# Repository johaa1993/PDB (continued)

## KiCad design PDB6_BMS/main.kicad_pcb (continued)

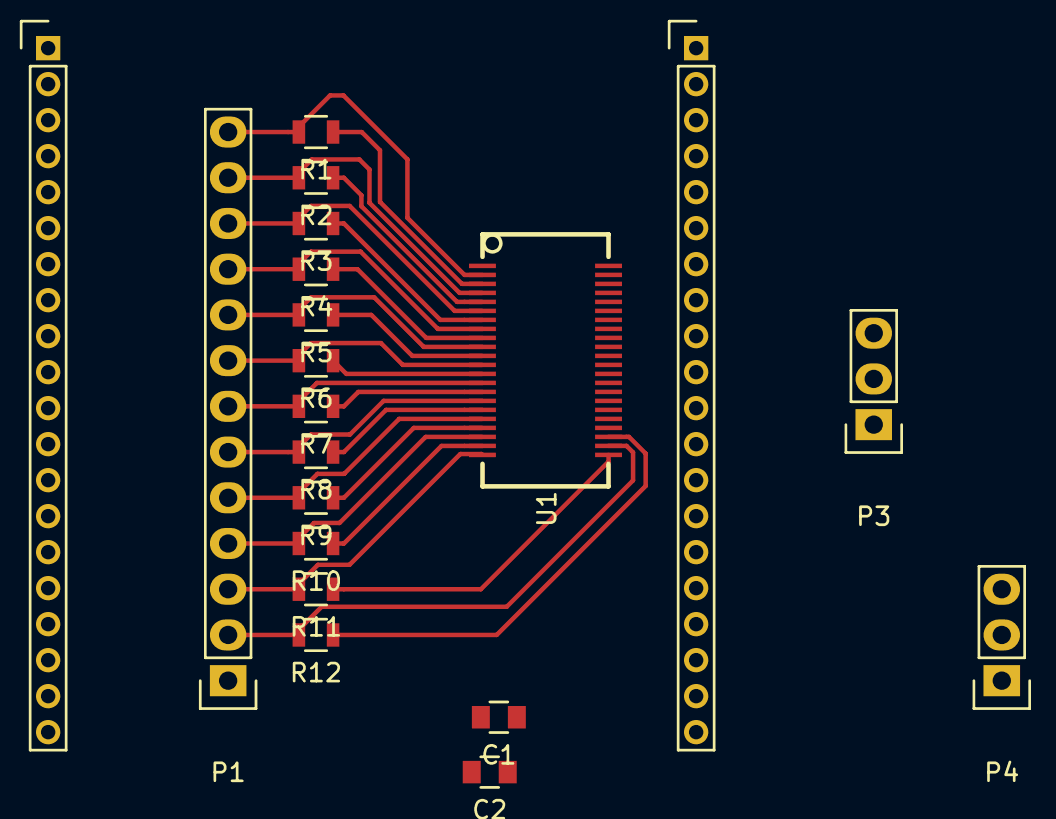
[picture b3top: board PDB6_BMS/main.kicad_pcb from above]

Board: 2 copper layers, 20 parts (0 on the bottom side), 33 nets.

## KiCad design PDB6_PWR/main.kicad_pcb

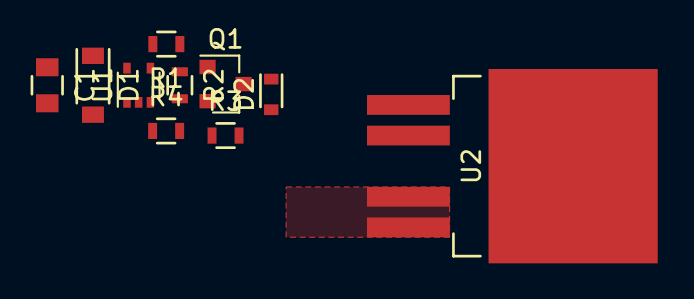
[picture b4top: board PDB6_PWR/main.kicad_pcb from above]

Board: 2 copper layers, 10 parts (0 on the bottom side), 7 nets, no tracks yet.

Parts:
C1: C; C_0805
D1: 5V; SOD-123
D2: D; D_0603
Q1: BC847CE6327HTSA1; SOT-23
R1, R2, R3, R4: R; R_0603
U1: 74LVC1G08; SOT-353
U2: AUIPS7111S; TO-263-5Lead

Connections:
+3V3: C1.1, D1.1, U1.5
/Power_Out: U2.4, U2.5
GND: C1.2, D1.2, D2.2, Q1.2, R2.2, R4.1, U1.3
unnamed: D2.1, Q1.3, U2.1
unnamed: Q1.1, R1.1, R2.1
unnamed: R1.2, U1.4
unnamed: R3.1, R4.2, U2.2

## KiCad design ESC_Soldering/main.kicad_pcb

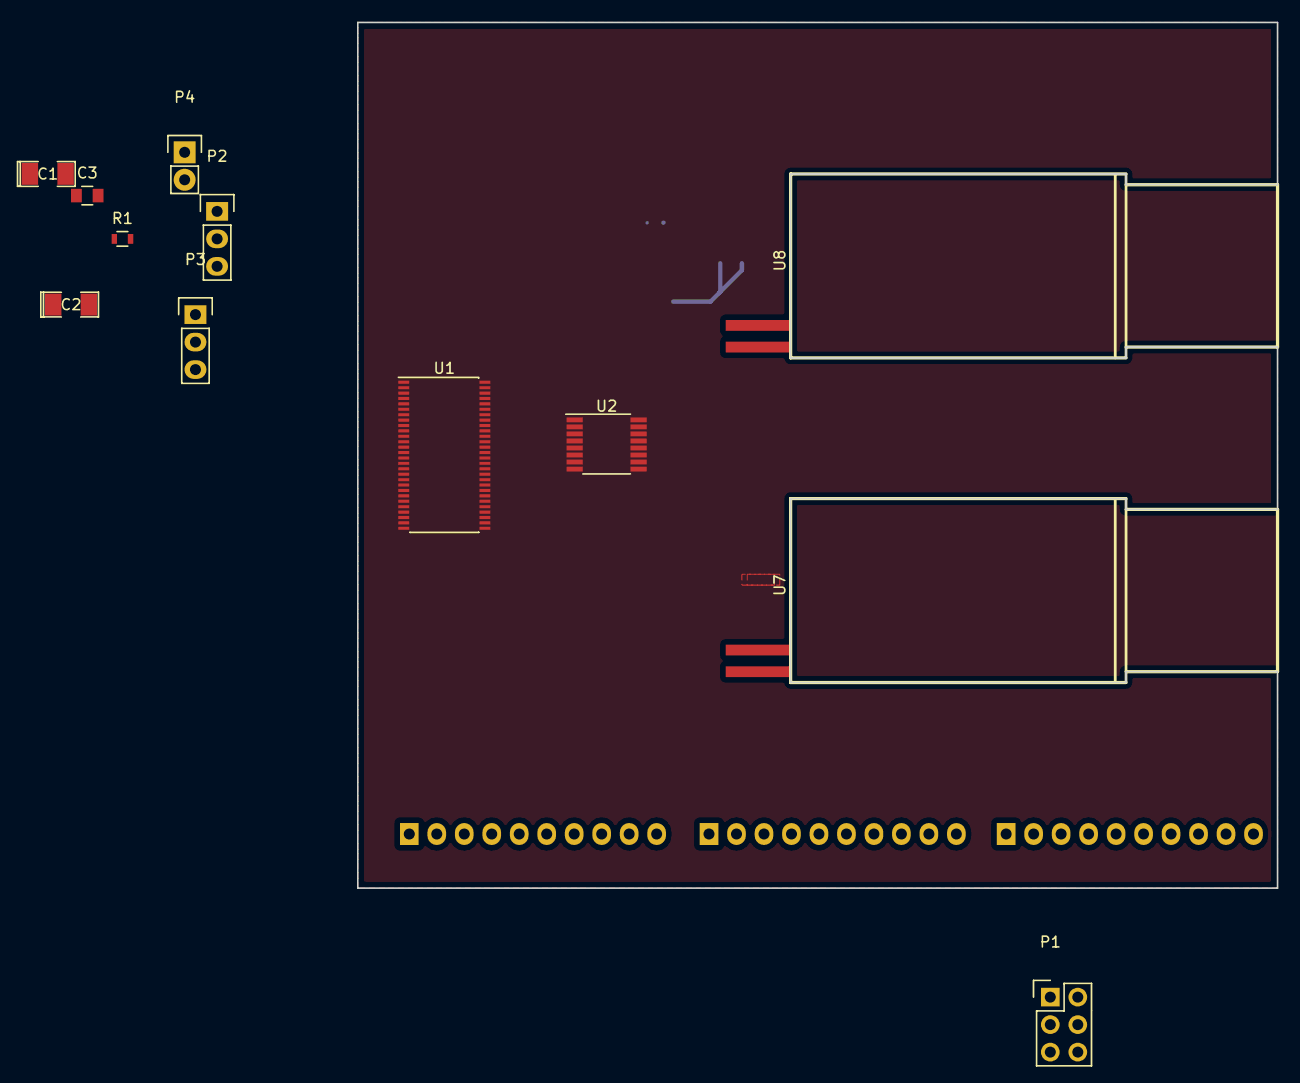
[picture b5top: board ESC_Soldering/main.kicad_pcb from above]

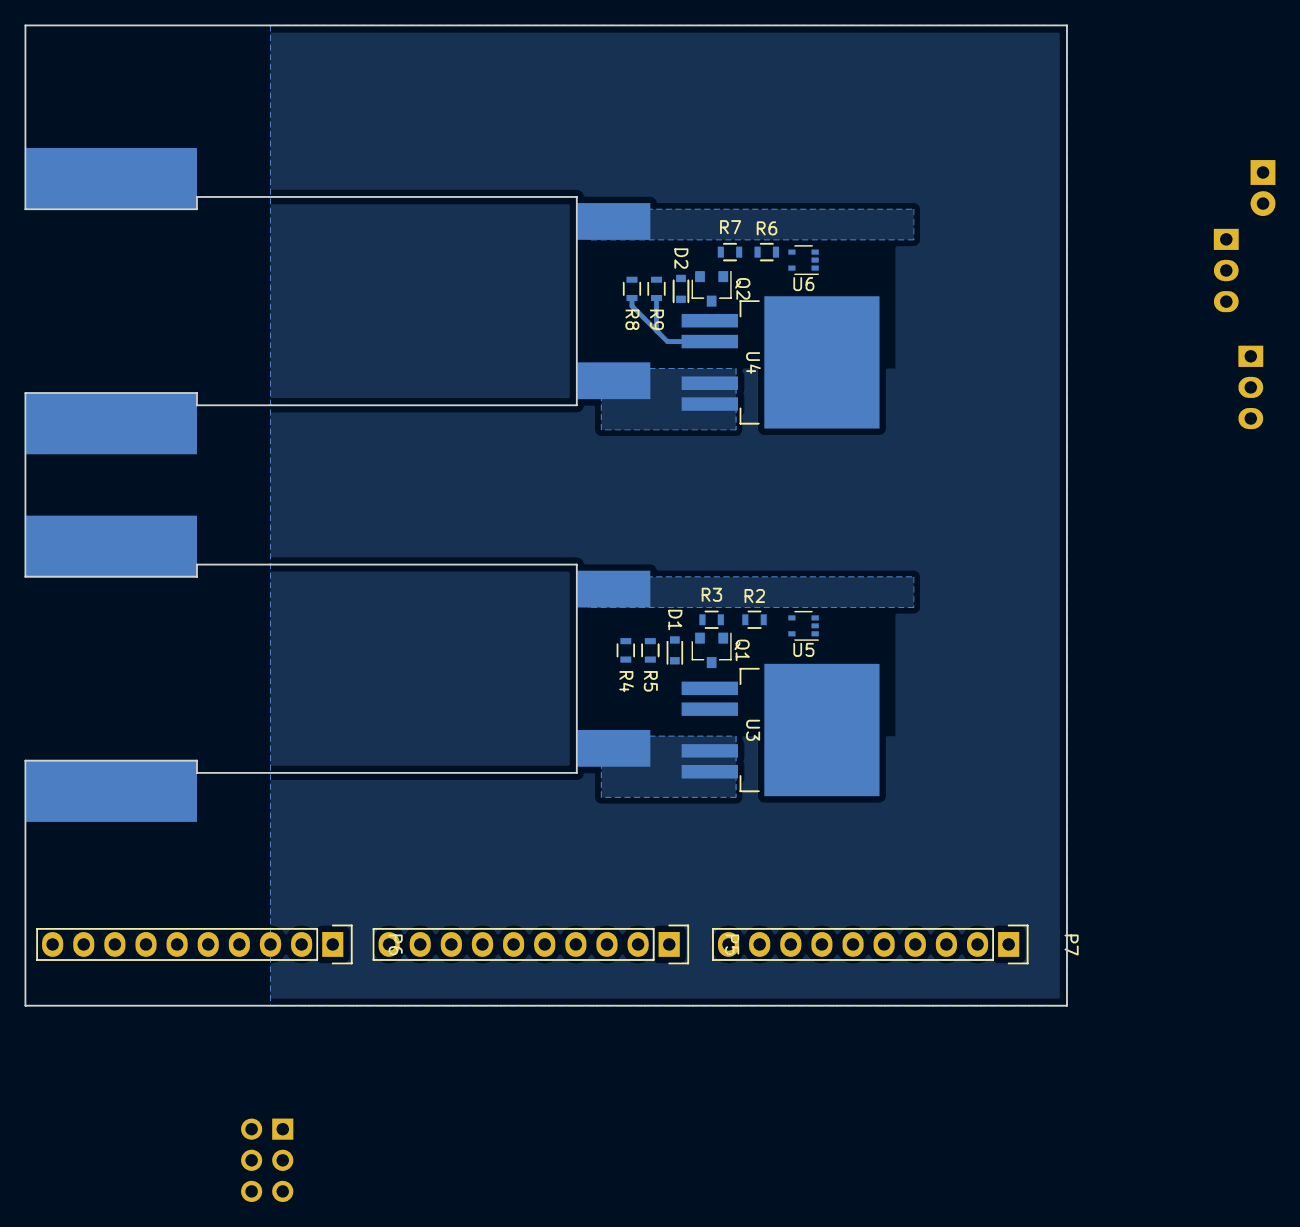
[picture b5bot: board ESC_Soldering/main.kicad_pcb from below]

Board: 2 copper layers, 85.0 x 80.0 mm, 31 parts (19 on the bottom side), 32 nets.

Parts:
C1, C2: CP; SMD-1206_Pol
C3: C; C_0805
D1, D2: D; D_0603
P1: CONN_02X03; Pin_Header_Straight_2x03
P2, P3: CONN_01X03; Pin_Header_Straight_1x03
P4: CONN_01X02; Pin_Header_Straight_1x02
P5, P6, P7: CONN_01X10; Pin_Header_Straight_1x10
Q1, Q2: BC847CE6327HTSA1; SOT-23
R1, R2, R3, R4, R5, R6, R7, R8, R9: R; R_0603
U1: PCA9698; TSSOP-56_6.1x14mm_Pitch0.5mm
U2: ADS7828; TSSOP-16_4.4x5mm_Pitch0.65mm
U3, U4: AUIPS7111S; TO-263-5Lead
U5, U6: 74LVC1G08; SOT-353
U7, U8: Littlebee

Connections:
+3V3: C1.1, P1.2, P2.3, P3.3, P4.1, R1.2, U1.18, U1.46, U5.5, U6.5
+BATT: U3.3, U4.3
/CH1: P7.1, R4.2, U2.1
/CH2: P7.2, R8.2, U2.2
/CH3: P7.3, U2.3
/CH4: P7.4, U2.4
/CH5: P7.5, U2.5
/CH6: P7.6, U2.6
/CH7: P7.7, U2.7
/CH8: P7.8, U2.8
/Enable_1: P5.1, U1.3, U5.1
/Enable_2: P5.2, U1.4, U6.1
/PWM1: P6.1, U7.4
/PWM2: P6.2, U8.4
/SCL: P1.5, U1.2, U2.14
/SDA: P1.3, U1.1, U2.15
/pwr_mod_1/Power_Enanle_B: P4.2, U5.2, U6.2
/pwr_mod_1/Power_Out: U3.4, U3.5, U7.1
/pwr_mod_2/Power_Out: U4.4, U4.5, U8.1
GND: C1.2, C2.2, C3.2, D1.2, D2.2, P1.1, P2.1, P3.1, Q1.2, Q2.2, R3.2, R5.1, R7.2, R9.1, U1.6, U1.11, U1.23, U1.34, U1.39, U1.51, U2.9, U2.11, U5.3, U6.3, U7.2, U7.3, U8.2, U8.3
unnamed: C2.1, R1.1, U2.16
unnamed: C3.1, U2.10
unnamed: D1.1, Q1.3, U3.1
unnamed: D2.1, Q2.3, U4.1
unnamed: P2.2, U2.13
unnamed: P3.2, U2.12
unnamed: Q1.1, R2.1, R3.1
unnamed: Q2.1, R6.1, R7.1
unnamed: R2.2, U5.4
unnamed: R4.1, R5.2, U3.2
unnamed: R6.2, U6.4
unnamed: R8.1, R9.2, U4.2

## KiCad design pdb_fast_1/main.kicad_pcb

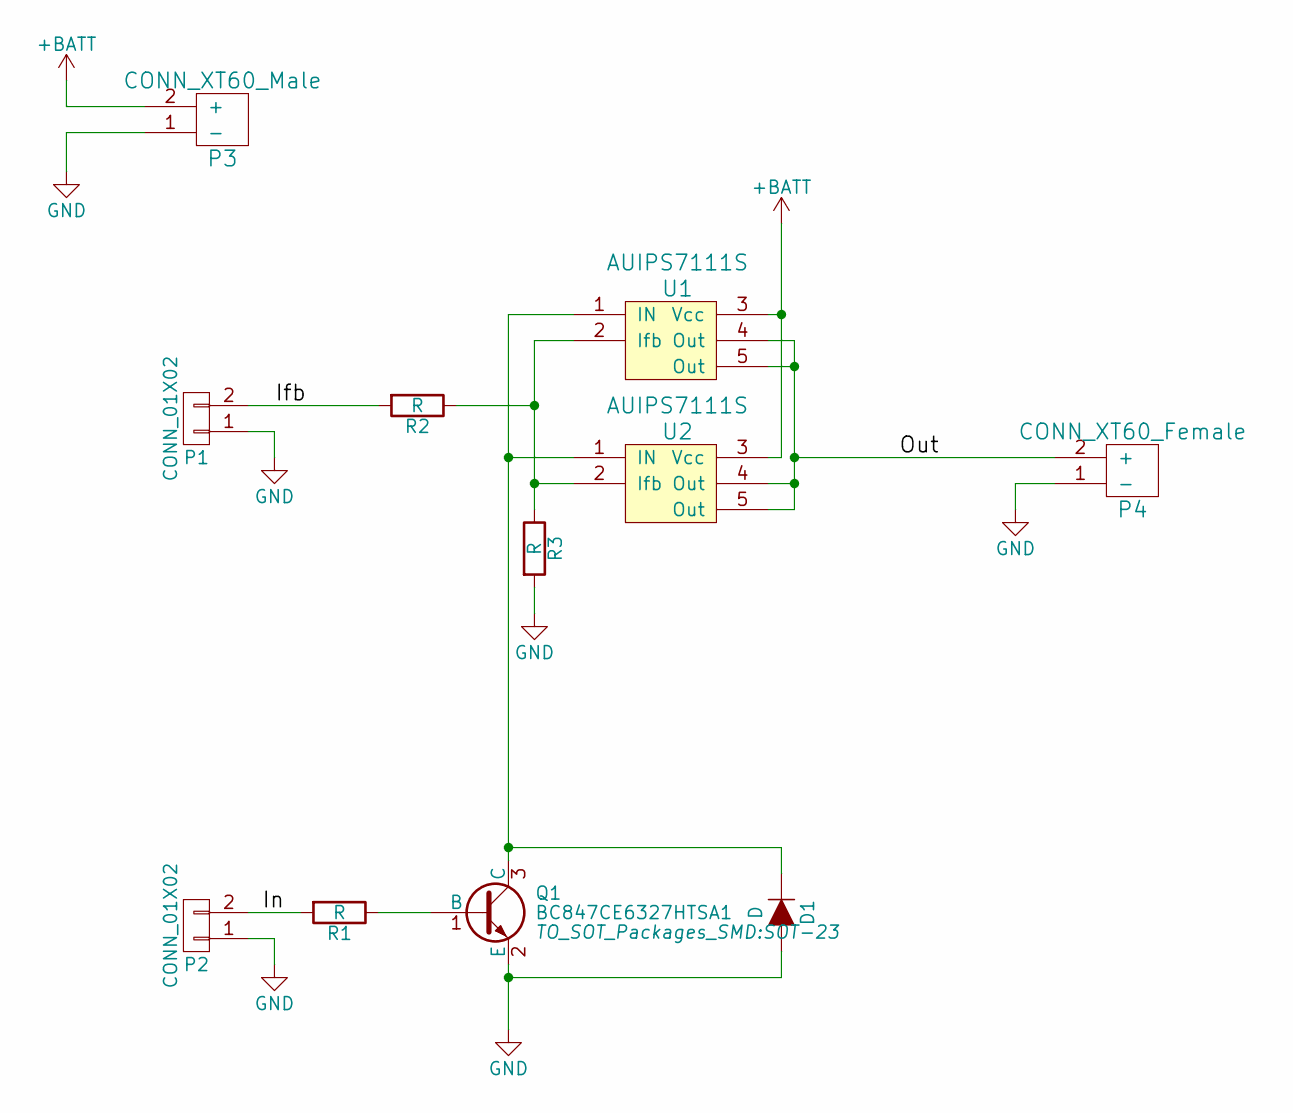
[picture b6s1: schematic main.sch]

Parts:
D1: D; SOD-123
P1, P2: CONN_01X02; Pin_Header_Straight_1x02
P3: CONN_XT60_Male; CONN_XT60_Male1_Horizontal
P4: CONN_XT60_Female; CONN_XT60_Male2_Horizontal
Q1: BC847CE6327HTSA1; SOT-23
R1, R2, R3: R; R_0603
U1, U2: AUIPS7111S; TO-263-!3

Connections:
+BATT: P3.2 (+), U1.3 (Vcc), U2.3 (Vcc)
/Ifb: P1.2, R2.2
/In: P2.2, R1.2
/Out: P4.2 (+), U1.4 (Out), U1.5 (Out), U2.4 (Out), U2.5 (Out)
GND: D1.2 (A), P1.1, P2.1, P3.1 (-), P4.1 (-), Q1.2 (E), R3.2
unnamed: D1.1 (K), Q1.3 (C), U1.1 (IN), U2.1 (IN)
unnamed: Q1.1 (B), R1.1
unnamed: R2.1, R3.1, U1.2 (Ifb), U2.2 (Ifb)

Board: 2 copper layers, 11 parts (0 on the bottom side), 8 nets, no tracks yet.

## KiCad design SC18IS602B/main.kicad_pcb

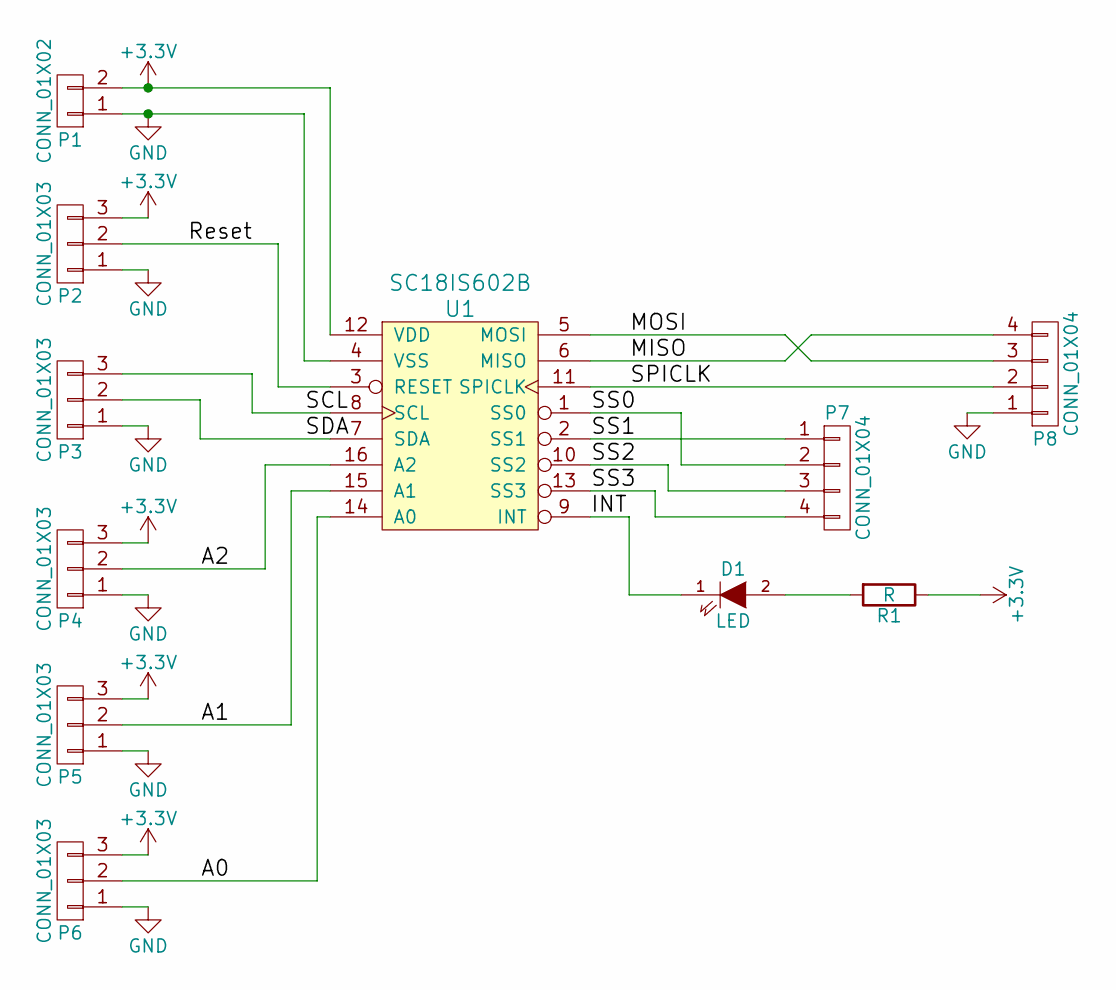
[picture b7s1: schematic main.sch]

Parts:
D1: LED; LED_0805
P1: CONN_01X02; Pin_Header_Straight_1x02
P2, P3, P4, P5, P6: CONN_01X03; Pin_Header_Straight_1x03
P7, P8: CONN_01X04; Pin_Header_Straight_1x04
R1: R; Resistor_Horizontal_RM7mm
U1: SC18IS602B; TSSOP-16_4.4x5mm_Pitch0.65mm

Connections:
+3V3: P1.2, P2.3, P4.3, P5.3, P6.3, R1.1, U1.12 (VDD)
/A0: P6.2, U1.14 (A0)
/A1: P5.2, U1.15 (A1)
/A2: P4.2, U1.16 (A2)
/INT: D1.1 (K), U1.9 (INT)
/MISO: P8.4, U1.6 (MISO)
/MOSI: P8.3, U1.5 (MOSI)
/Reset: P2.2, U1.3 (RESET)
/SCL: P3.3, U1.8 (SCL)
/SDA: P3.2, U1.7 (SDA)
/SPICLK: P8.2, U1.11 (SPICLK)
/SS0: P7.2, U1.1 (SS0)
/SS1: P7.1, U1.2 (SS1)
/SS2: P7.3, U1.10 (SS2)
/SS3: P7.4, U1.13 (SS3)
GND: P1.1, P2.1, P3.1, P4.1, P5.1, P6.1, P8.1, U1.4 (VSS)
unnamed: D1.2 (A), R1.2

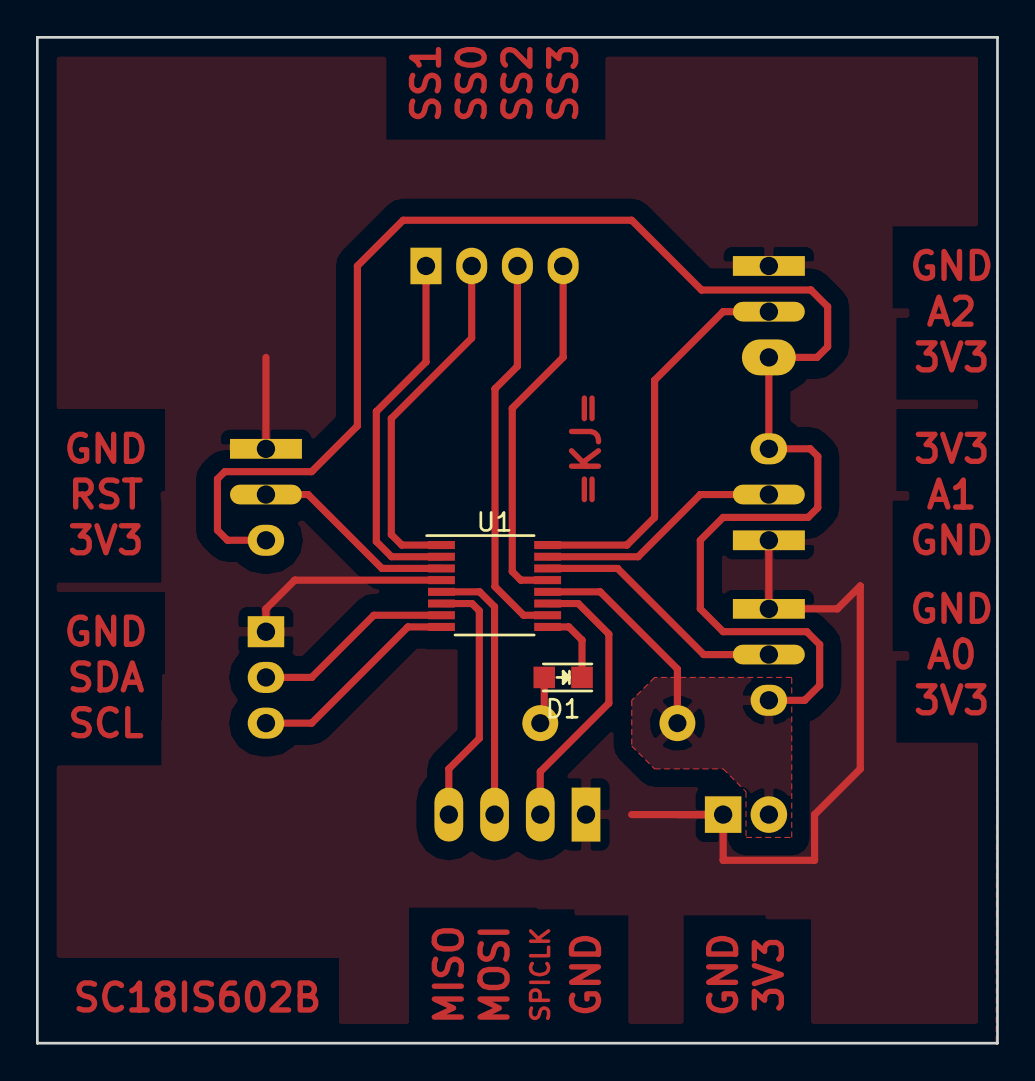
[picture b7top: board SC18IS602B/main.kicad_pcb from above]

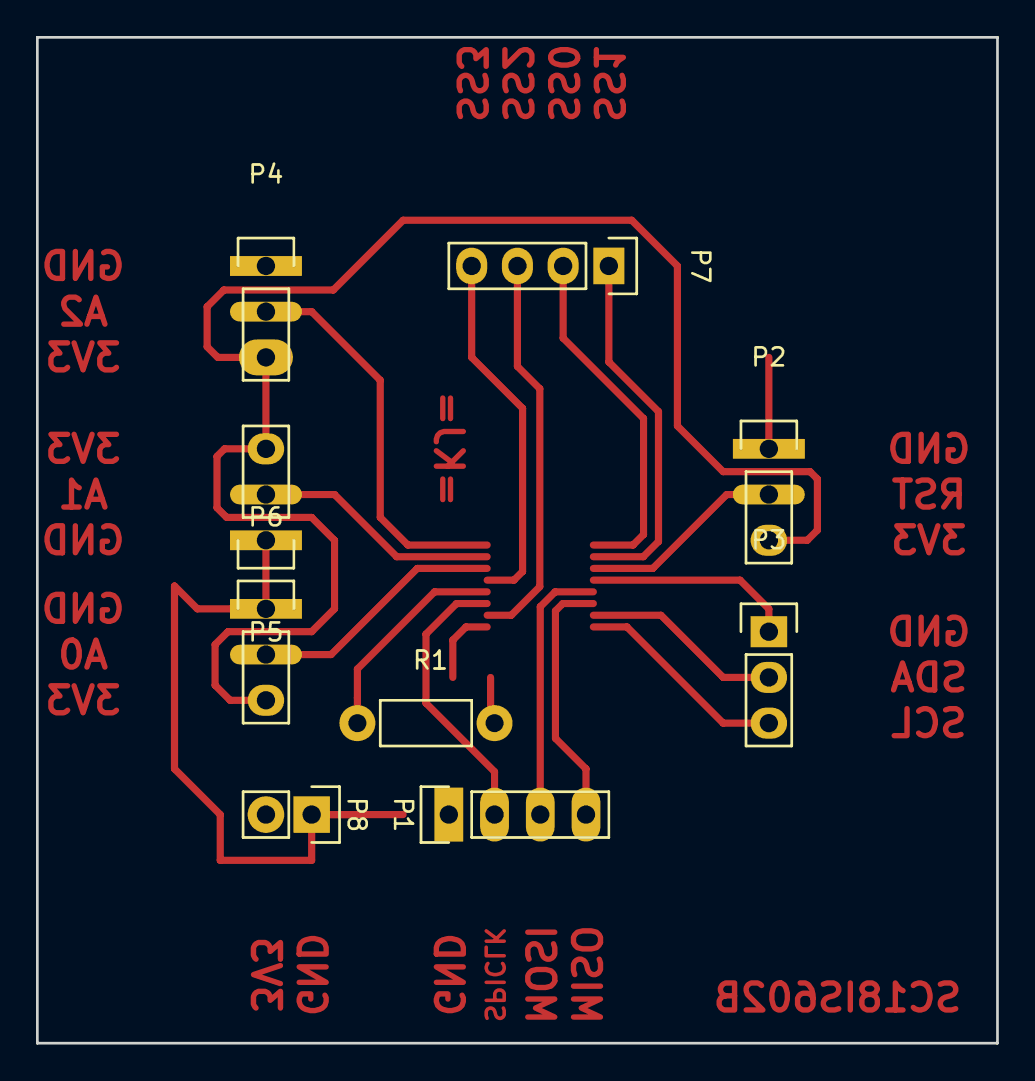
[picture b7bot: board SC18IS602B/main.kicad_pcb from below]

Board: 2 copper layers, 53.3 x 55.9 mm, 11 parts (9 on the bottom side), 17 nets.

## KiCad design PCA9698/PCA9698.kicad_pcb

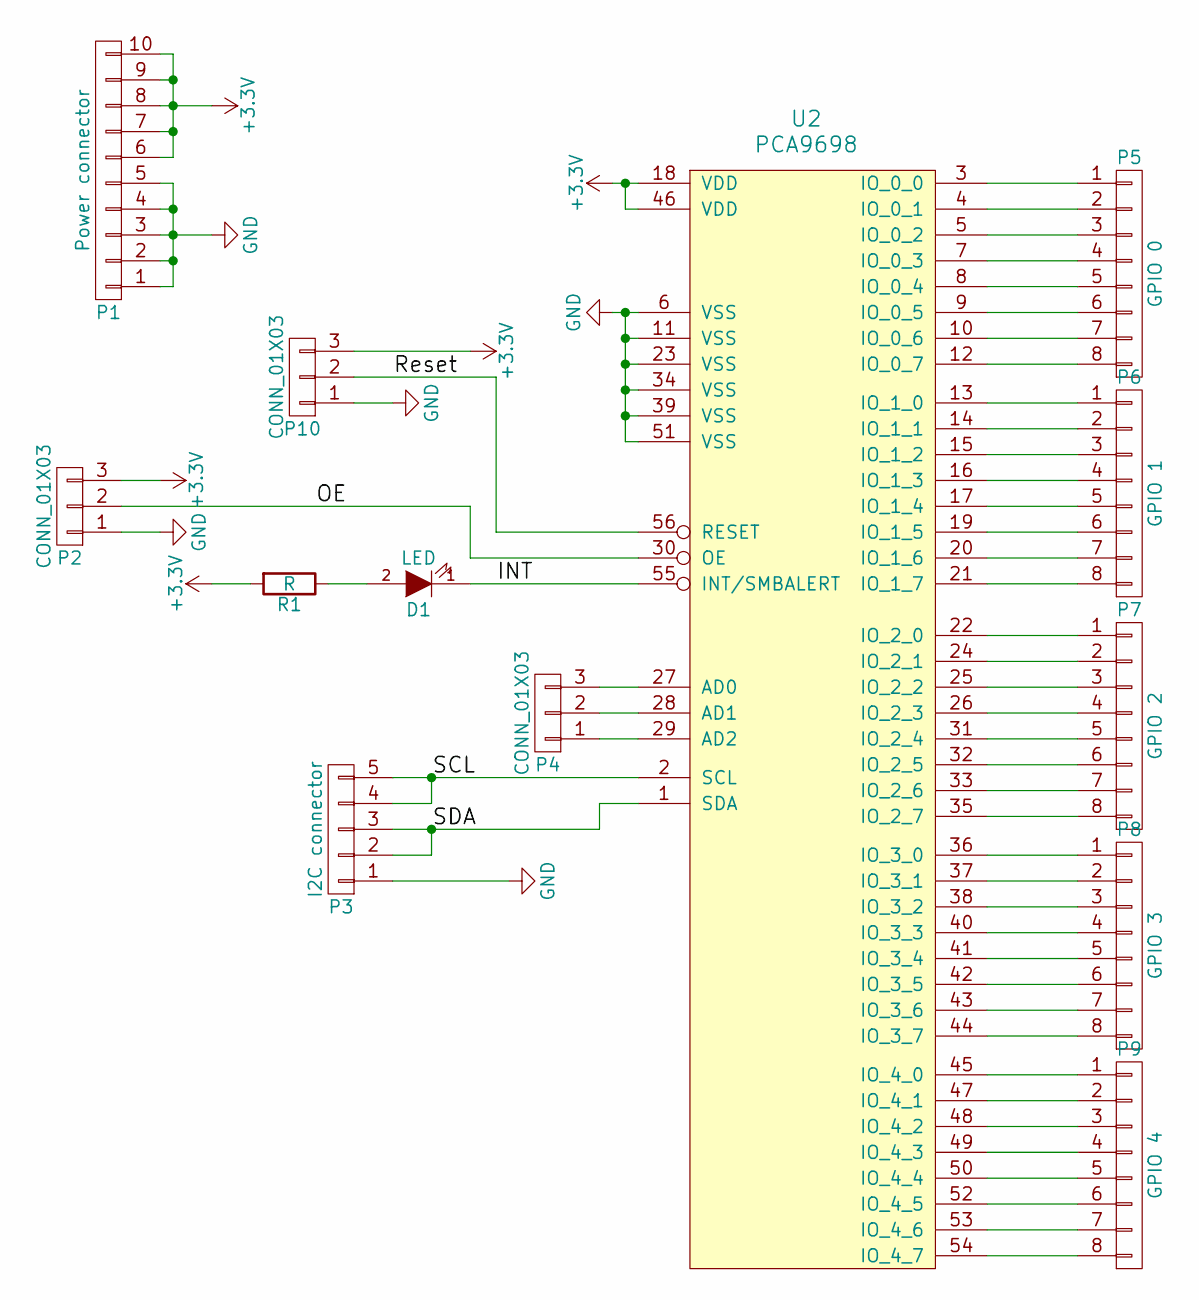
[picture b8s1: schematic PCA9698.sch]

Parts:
D1: LED; LED_0805
P1: Power connector; Pin_Header_Straight_1x10
P2, P4, P10: CONN_01X03; Pin_Header_Straight_1x03
P3: I2C connector; Pin_Header_Straight_1x05
P5: GPIO 0; Pin_Header_Straight_1x08
P6: GPIO 1; Pin_Header_Straight_1x08
P7: GPIO 2; Pin_Header_Straight_1x08
P8: GPIO 3; Pin_Header_Straight_1x08
P9: GPIO 4; Pin_Header_Straight_1x08
R1: R; R_0805
U2: PCA9698; TSSOP-56_6.1x14mm_Pitch0.5mm

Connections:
+3V3: P1.6, P1.7, P1.8, P1.9, P1.10, P2.3, P10.3, R1.2, U2.18 (VDD), U2.46 (VDD)
/INT: D1.1 (K), U2.55 (INT/SMBALERT)
/OE: P2.2, U2.30 (OE)
/Reset: P10.2, U2.56 (RESET)
/SCL: P3.4, P3.5, U2.2 (SCL)
/SDA: P3.2, P3.3, U2.1 (SDA)
GND: P1.1, P1.2, P1.3, P1.4, P1.5, P2.1, P3.1, P10.1, U2.6 (VSS), U2.11 (VSS), U2.23 (VSS), U2.34 (VSS), U2.39 (VSS), U2.51 (VSS)
unnamed: D1.2 (A), R1.1
unnamed: P4.1, U2.29 (AD2)
unnamed: P4.2, U2.28 (AD1)
unnamed: P4.3, U2.27 (AD0)
unnamed: P5.1, U2.3 (IO_0_0)
unnamed: P5.2, U2.4 (IO_0_1)
unnamed: P5.3, U2.5 (IO_0_2)
unnamed: P5.4, U2.7 (IO_0_3)
unnamed: P5.5, U2.8 (IO_0_4)
unnamed: P5.6, U2.9 (IO_0_5)
unnamed: P5.7, U2.10 (IO_0_6)
unnamed: P5.8, U2.12 (IO_0_7)
unnamed: P6.1, U2.13 (IO_1_0)
unnamed: P6.2, U2.14 (IO_1_1)
unnamed: P6.3, U2.15 (IO_1_2)
unnamed: P6.4, U2.16 (IO_1_3)
unnamed: P6.5, U2.17 (IO_1_4)
unnamed: P6.6, U2.19 (IO_1_5)
unnamed: P6.7, U2.20 (IO_1_6)
unnamed: P6.8, U2.21 (IO_1_7)
unnamed: P7.1, U2.22 (IO_2_0)
unnamed: P7.2, U2.24 (IO_2_1)
unnamed: P7.3, U2.25 (IO_2_2)
unnamed: P7.4, U2.26 (IO_2_3)
unnamed: P7.5, U2.31 (IO_2_4)
unnamed: P7.6, U2.32 (IO_2_5)
unnamed: P7.7, U2.33 (IO_2_6)
unnamed: P7.8, U2.35 (IO_2_7)
unnamed: P8.1, U2.36 (IO_3_0)
unnamed: P8.2, U2.37 (IO_3_1)
unnamed: P8.3, U2.38 (IO_3_2)
unnamed: P8.4, U2.40 (IO_3_3)
unnamed: P8.5, U2.41 (IO_3_4)
unnamed: P8.6, U2.42 (IO_3_5)
unnamed: P8.7, U2.43 (IO_3_6)
unnamed: P8.8, U2.44 (IO_3_7)
unnamed: P9.1, U2.45 (IO_4_0)
unnamed: P9.2, U2.47 (IO_4_1)
unnamed: P9.3, U2.48 (IO_4_2)
unnamed: P9.4, U2.49 (IO_4_3)
unnamed: P9.5, U2.50 (IO_4_4)
unnamed: P9.6, U2.52 (IO_4_5)
unnamed: P9.7, U2.53 (IO_4_6)
unnamed: P9.8, U2.54 (IO_4_7)

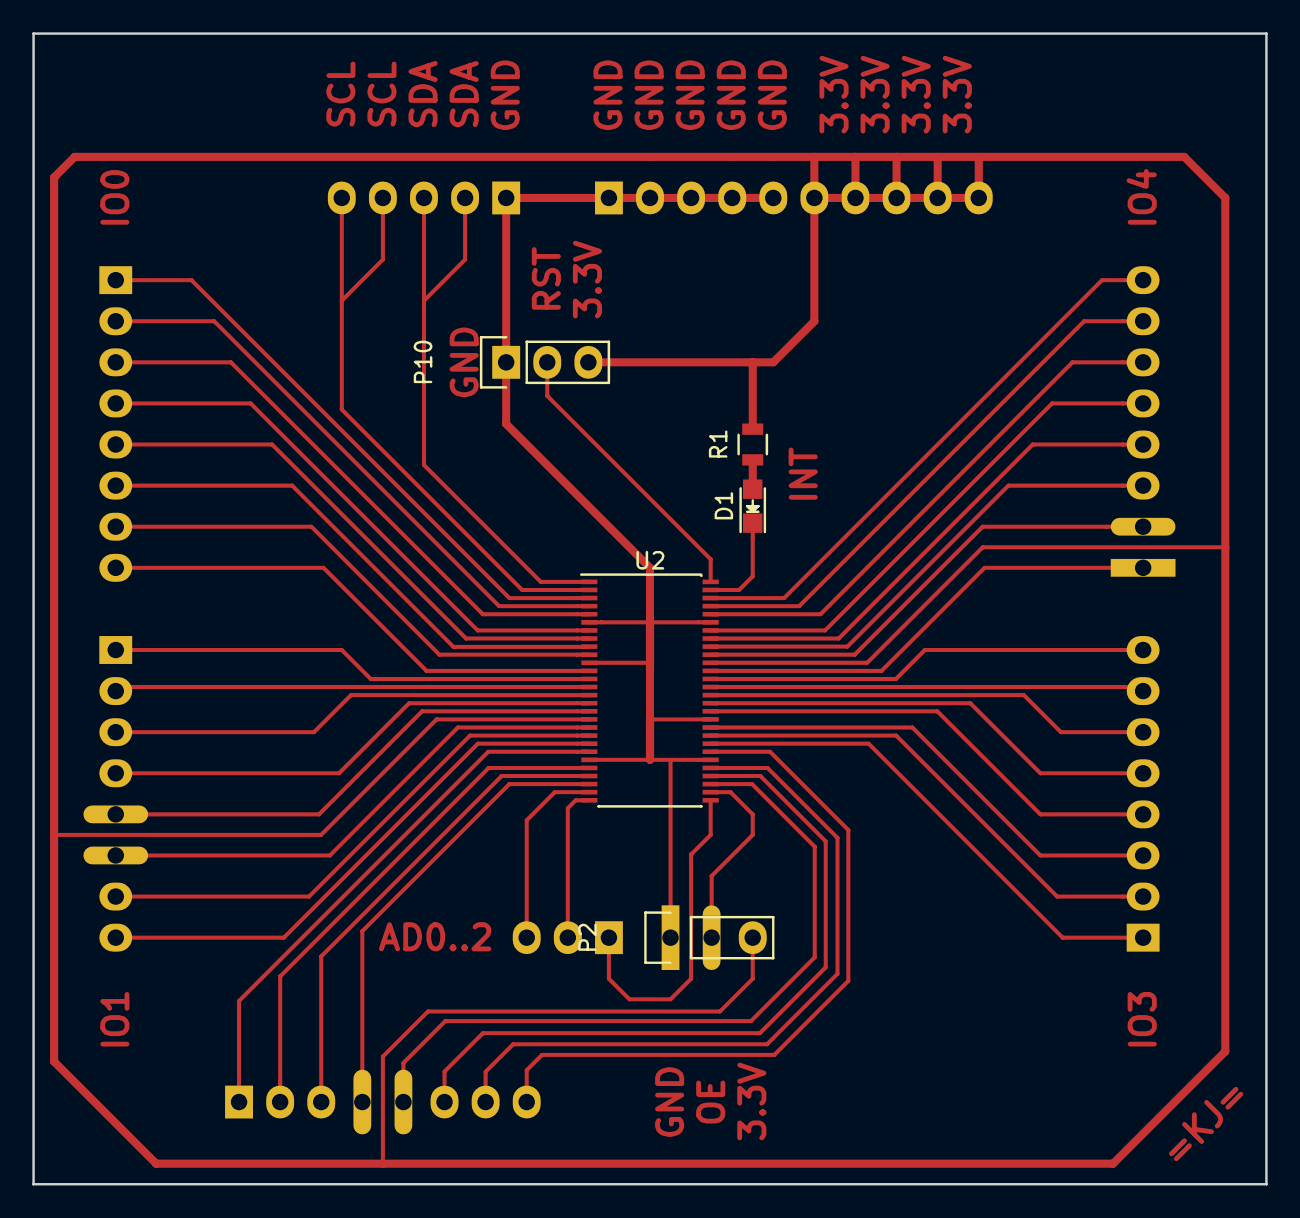
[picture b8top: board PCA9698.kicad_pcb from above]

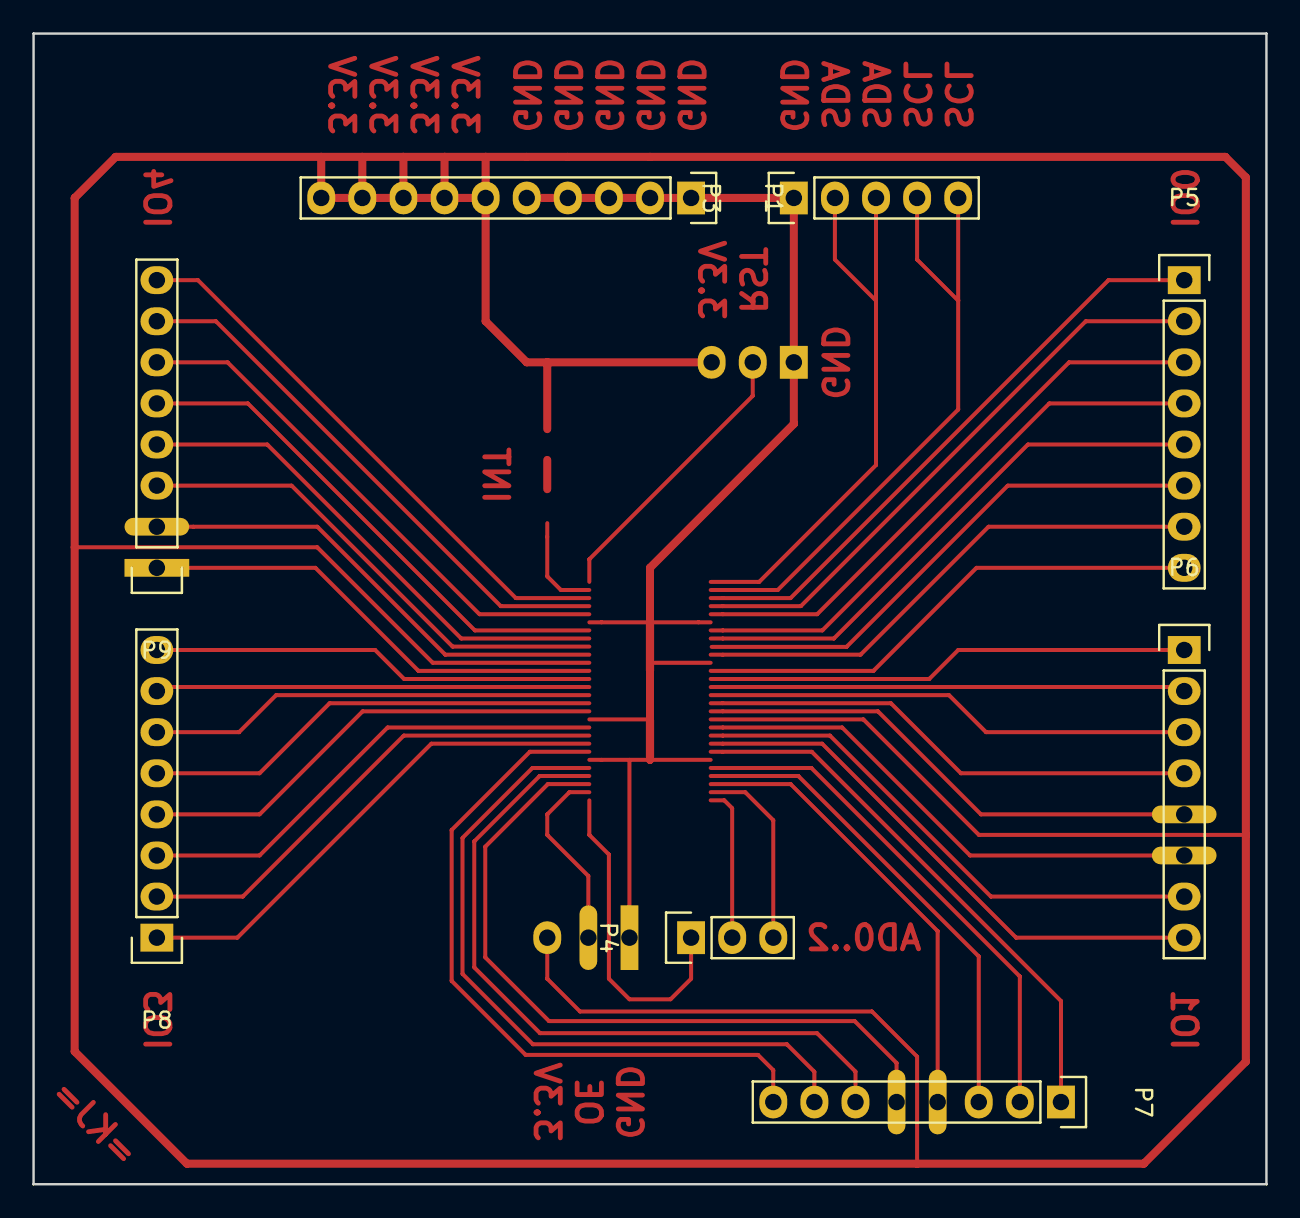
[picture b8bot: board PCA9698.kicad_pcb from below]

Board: 4 copper layers, 76.2 x 71.1 mm, 13 parts (8 on the bottom side), 51 nets.

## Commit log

2016-10-29 my init readme
2016-11-02 test
